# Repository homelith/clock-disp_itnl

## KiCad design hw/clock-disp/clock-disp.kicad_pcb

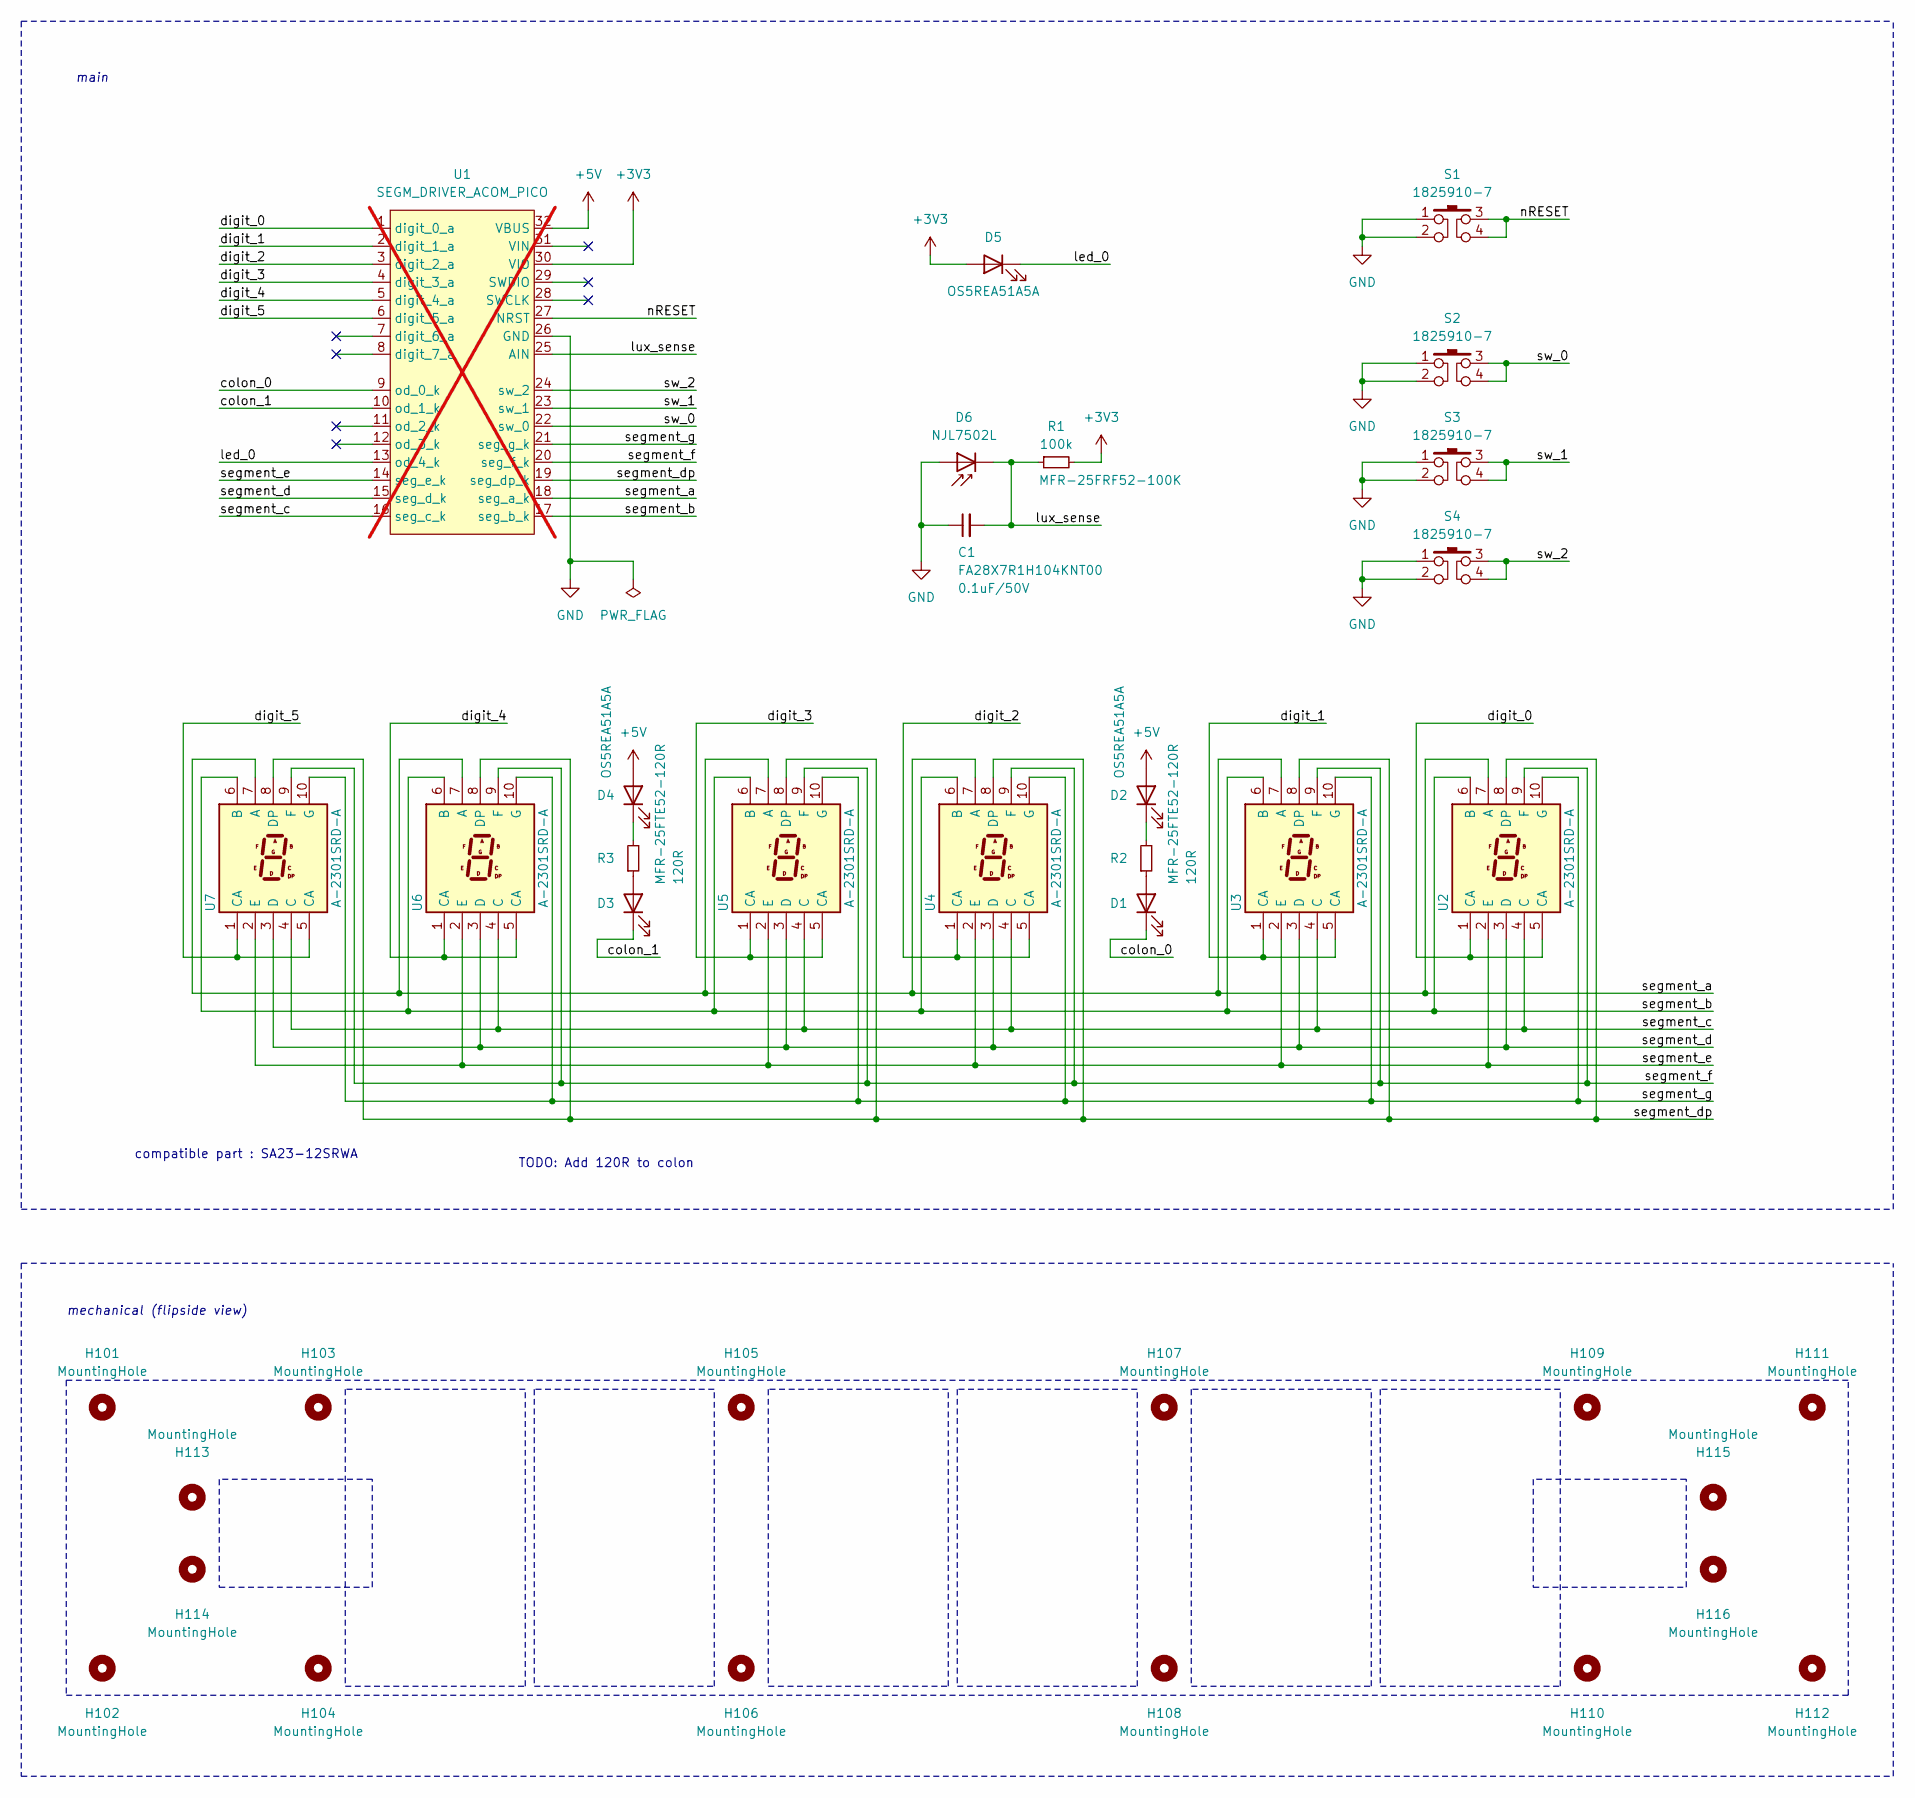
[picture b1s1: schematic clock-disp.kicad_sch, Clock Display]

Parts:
C1: FA28X7R1H104KNT00
D1, D2, D3, D4, D5: OS5REA51A5A
D6: NJL7502L
H101, H102, H103, H104, H105, H106, H107, H108, H109, H110, H111, H112, H113, H114, H115, H116: MountingHole; MountingHole_3.2mm_M3
R1: MFR-25FRF52-100K
R2, R3: MFR-25FTE52-120R
S1, S2, S3, S4: 1825910-7
U1: SEGM_DRIVER_ACOM_PICO; SEGM_DRIVER_ACOM_Pico; not fitted
U2, U3, U4, U5, U6, U7: A-2301SRD-A

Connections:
+3V3: D5.2 (A), R1.2, U1.30 (VIO)
+5V: D2.2 (A), D4.2 (A), U1.32 (VBUS)
/colon_0: D1.1 (K), U1.9 (od_0_k)
/colon_1: D3.1 (K), U1.10 (od_1_k)
/digit_0: U1.1 (digit_0_a), U2.1 (CA), U2.5 (CA)
/digit_1: U1.2 (digit_1_a), U3.1 (CA), U3.5 (CA)
/digit_2: U1.3 (digit_2_a), U4.1 (CA), U4.5 (CA)
/digit_3: U1.4 (digit_3_a), U5.1 (CA), U5.5 (CA)
/digit_4: U1.5 (digit_4_a), U6.1 (CA), U6.5 (CA)
/digit_5: U1.6 (digit_5_a), U7.1 (CA), U7.5 (CA)
/led_0: D5.1 (K), U1.13 (od_4_k)
/lux_sense: C1.2, D6.1 (K), R1.1, U1.25 (AIN)
/nRESET: S1.3, S1.4, U1.27 (NRST)
/segment_a: U1.18 (seg_a_k), U2.7 (A), U3.7 (A), U4.7 (A), U5.7 (A), U6.7 (A), U7.7 (A)
/segment_b: U1.17 (seg_b_k), U2.6 (B), U3.6 (B), U4.6 (B), U5.6 (B), U6.6 (B), U7.6 (B)
/segment_c: U1.16 (seg_c_k), U2.4 (C), U3.4 (C), U4.4 (C), U5.4 (C), U6.4 (C), U7.4 (C)
/segment_d: U1.15 (seg_d_k), U2.3 (D), U3.3 (D), U4.3 (D), U5.3 (D), U6.3 (D), U7.3 (D)
/segment_dp: U1.19 (seg_dp_k), U2.8 (DP), U3.8 (DP), U4.8 (DP), U5.8 (DP), U6.8 (DP), U7.8 (DP)
/segment_e: U1.14 (seg_e_k), U2.2 (E), U3.2 (E), U4.2 (E), U5.2 (E), U6.2 (E), U7.2 (E)
/segment_f: U1.20 (seg_f_k), U2.9 (F), U3.9 (F), U4.9 (F), U5.9 (F), U6.9 (F), U7.9 (F)
/segment_g: U1.21 (seg_g_k), U2.10 (G), U3.10 (G), U4.10 (G), U5.10 (G), U6.10 (G), U7.10 (G)
/sw_0: S2.3, S2.4, U1.22 (sw_0)
/sw_1: S3.3, S3.4, U1.23 (sw_1)
/sw_2: S4.3, S4.4, U1.24 (sw_2)
GND: C1.1, D6.2 (A), S1.1, S1.2, S2.1, S2.2, S3.1, S3.2, S4.1, S4.2, U1.26 (GND)
unnamed: D1.2 (A), R2.1
unnamed: D2.1 (K), R2.2
unnamed: D3.2 (A), R3.1
unnamed: D4.1 (K), R3.2

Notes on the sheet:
TODO: Add 120R to colon
compatible part : SA23-12SRWA
mechanical (flipside view)
main

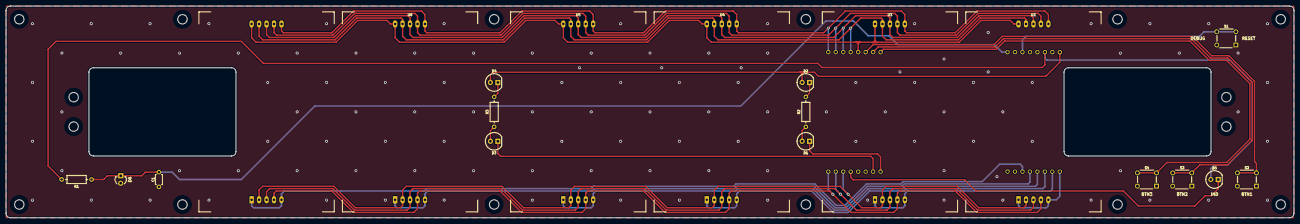
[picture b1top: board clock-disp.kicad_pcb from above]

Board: 2 copper layers, 438.0 x 72.0 mm, 37 parts (1 on the bottom side), 29 nets.

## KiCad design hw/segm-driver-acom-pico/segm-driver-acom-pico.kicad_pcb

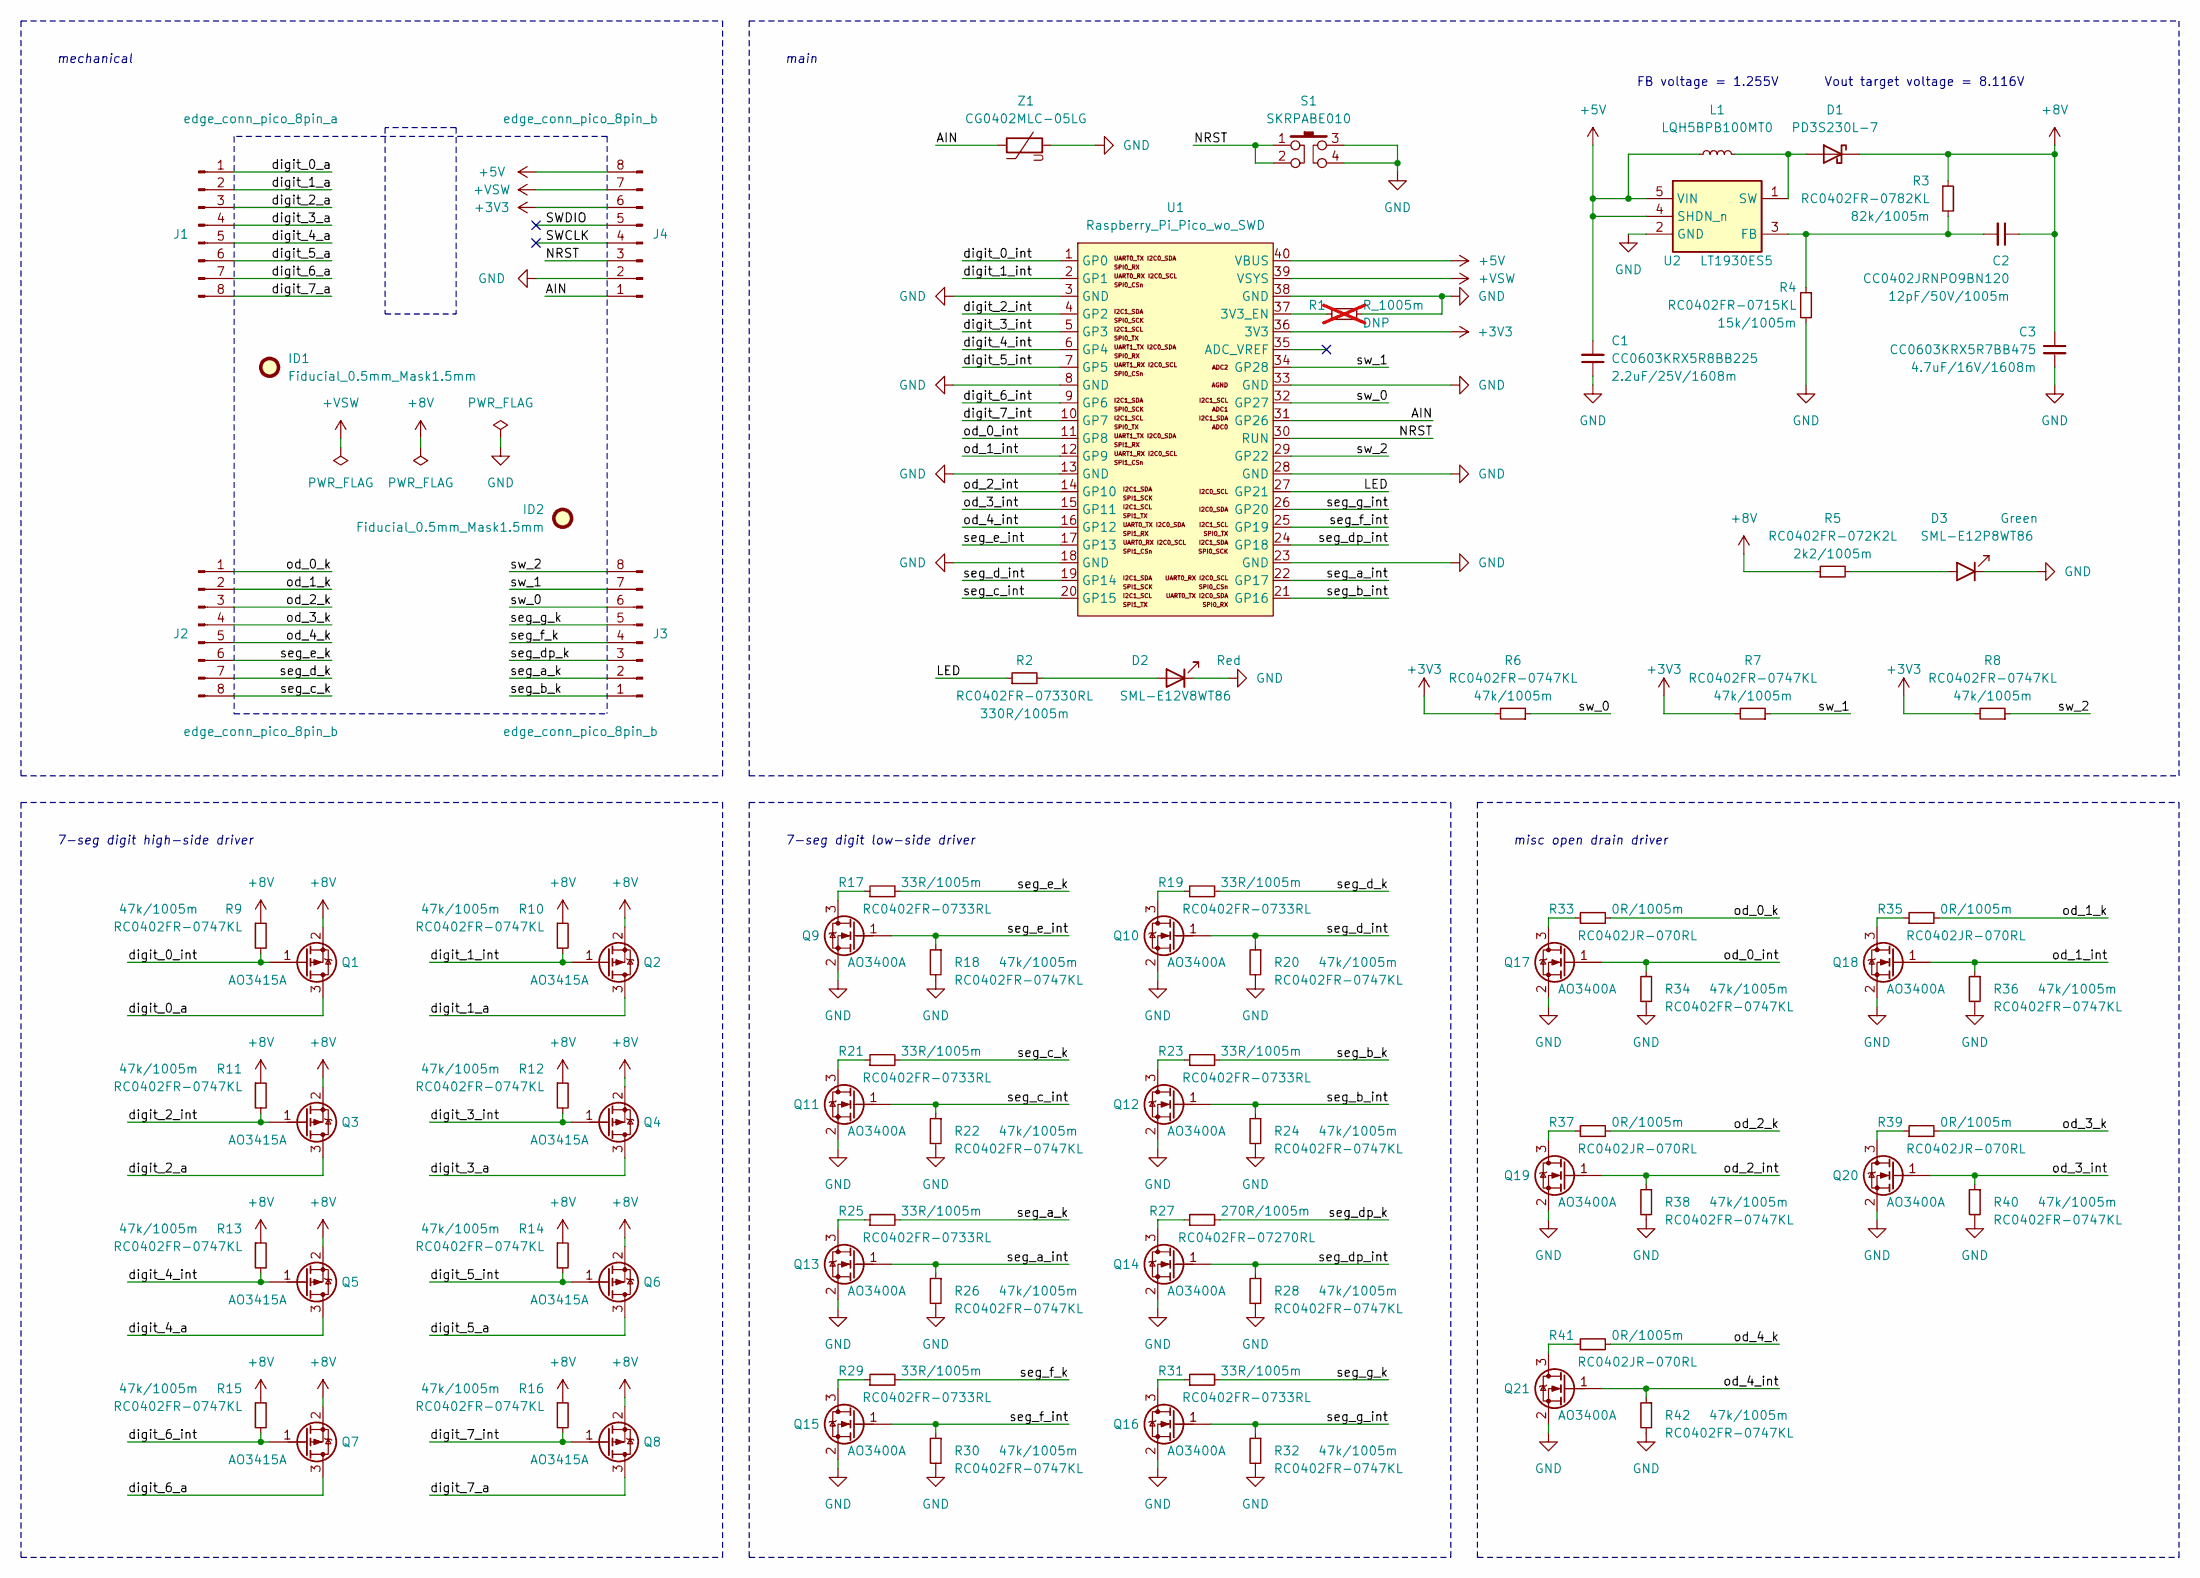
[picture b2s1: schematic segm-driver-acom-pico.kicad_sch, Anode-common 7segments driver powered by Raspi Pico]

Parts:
C1: CC0603KRX5R8BB225
C2: CC0402JRNPO9BN120
C3: CC0603KRX5R7BB475
D1: PD3S230L-7
D2: SML-E12V8WT86
D3: SML-E12P8WT86
ID1, ID2: Fiducial_0.5mm_Mask1.5mm
J1: edge_conn_pico_8pin_a
J2, J3, J4: edge_conn_pico_8pin_b
L1: LQH5BPB100MT0
Q1, Q2, Q3, Q4, Q5, Q6, Q7, Q8: AO3415A
Q9, Q10, Q11, Q12, Q13, Q14, Q15, Q16, Q17, Q18, Q19, Q20, Q21: AO3400A
R1: R_1005m; not fitted
R2: RC0402FR-07330RL
R3: RC0402FR-0782KL
R4: RC0402FR-0715KL
R5: RC0402FR-072K2L
R6, R7, R8, R9, R10, R11, R12, R13, R14, R15, R16, R18, R20, R22, R24, R26, R28, R30, R32, R34, R36, R38, R40, R42: RC0402FR-0747KL
R17, R19, R21, R23, R25, R29, R31: RC0402FR-0733RL
R27: RC0402FR-07270RL
R33, R35, R37, R39, R41: RC0402JR-070RL
S1: SKRPABE010
U1: Raspberry_Pi_Pico_wo_SWD
U2: LT1930ES5
Z1: CG0402MLC-05LG

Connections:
+3V3: J4.6, R6.2, R7.2, R8.2, U1.36 (3V3)
+5V: C1.2, J4.8, L1.1, U1.40 (VBUS), U2.4 (SHDN_n), U2.5 (VIN)
+8V: C2.1, C3.1, D1.2 (K), Q1.2 (S), Q2.2 (S), Q3.2 (S), Q4.2 (S), Q5.2 (S), Q6.2 (S), Q7.2 (S), Q8.2 (S), R3.1, R5.1, R9.1, R10.1, R11.1, R12.1, R13.1, R14.1, R15.1, R16.1
+VSW: J4.7, U1.39 (VSYS)
/AIN: J4.1, U1.31 (GP26), Z1.1
/LED: R2.1, U1.27 (GP21)
/NRST: J4.3, S1.1, S1.2, U1.30 (RUN)
/SWCLK: J4.4
/SWCLK_1: J4.4
/SWCLK_2: J4.4
/SWDIO: J4.5
/SWDIO_1: J4.5
/SWDIO_2: J4.5
/digit_0_a: J1.1, Q1.3 (D)
/digit_0_int: Q1.1 (G), R9.2, U1.1 (GP0)
/digit_1_a: J1.2, Q2.3 (D)
/digit_1_int: Q2.1 (G), R10.2, U1.2 (GP1)
/digit_2_a: J1.3, Q3.3 (D)
/digit_2_int: Q3.1 (G), R11.2, U1.4 (GP2)
/digit_3_a: J1.4, Q4.3 (D)
/digit_3_int: Q4.1 (G), R12.2, U1.5 (GP3)
/digit_4_a: J1.5, Q5.3 (D)
/digit_4_int: Q5.1 (G), R13.2, U1.6 (GP4)
/digit_5_a: J1.6, Q6.3 (D)
/digit_5_int: Q6.1 (G), R14.2, U1.7 (GP5)
/digit_6_a: J1.7, Q7.3 (D)
/digit_6_int: Q7.1 (G), R15.2, U1.9 (GP6)
/digit_7_a: J1.8, Q8.3 (D)
/digit_7_int: Q8.1 (G), R16.2, U1.10 (GP7)
/od_0_int: Q17.1 (G), R34.1, U1.11 (GP8)
/od_0_k: J2.1, R33.2
/od_1_int: Q18.1 (G), R36.1, U1.12 (GP9)
/od_1_k: J2.2, R35.2
/od_2_int: Q19.1 (G), R38.1, U1.14 (GP10)
/od_2_k: J2.3, R37.2
/od_3_int: Q20.1 (G), R40.1, U1.15 (GP11)
/od_3_k: J2.4, R39.2
/od_4_int: Q21.1 (G), R42.1, U1.16 (GP12)
/od_4_k: J2.5, R41.2
/seg_a_int: Q13.1 (G), R26.1, U1.22 (GP17)
/seg_a_k: J3.2, R25.2
/seg_b_int: Q12.1 (G), R24.1, U1.21 (GP16)
/seg_b_k: J3.1, R23.2
/seg_c_int: Q11.1 (G), R22.1, U1.20 (GP15)
/seg_c_k: J2.8, R21.2
/seg_d_int: Q10.1 (G), R20.1, U1.19 (GP14)
/seg_d_k: J2.7, R19.2
/seg_dp_int: Q14.1 (G), R28.1, U1.24 (GP18)
/seg_dp_k: J3.3, R27.2
/seg_e_int: Q9.1 (G), R18.1, U1.17 (GP13)
/seg_e_k: J2.6, R17.2
/seg_f_int: Q15.1 (G), R30.1, U1.25 (GP19)
/seg_f_k: J3.4, R29.2
/seg_g_int: Q16.1 (G), R32.1, U1.26 (GP20)
/seg_g_k: J3.5, R31.2
/sw_0: J3.6, R6.1, U1.32 (GP27)
/sw_1: J3.7, R7.1, U1.34 (GP28)
/sw_2: J3.8, R8.1, U1.29 (GP22)
GND: C1.1, C3.2, D2.1 (K), D3.1 (K), J4.2, Q9.2 (S), Q10.2 (S), Q11.2 (S), Q12.2 (S), Q13.2 (S), Q14.2 (S), Q15.2 (S), Q16.2 (S), Q17.2 (S), Q18.2 (S), Q19.2 (S), Q20.2 (S), Q21.2 (S), R1.2, R4.2, R18.2, R20.2, R22.2, R24.2, R26.2, R28.2, R30.2, R32.2, R34.2, R36.2, R38.2, R40.2, R42.2, S1.3, S1.4, U1.3 (GND), U1.8 (GND), U1.13 (GND), U1.18 (GND), U1.23 (GND), U1.28 (GND), U1.33 (GND), U1.38 (GND), U2.2 (GND), Z1.2
unnamed: D1.1 (A), L1.2, U2.1 (SW)
unnamed: D2.2 (A), R2.2
unnamed: D3.2 (A), R5.2
unnamed: Q9.3 (D), R17.1
unnamed: Q10.3 (D), R19.1
unnamed: Q11.3 (D), R21.1
unnamed: Q12.3 (D), R23.1
unnamed: Q13.3 (D), R25.1
unnamed: Q14.3 (D), R27.1
unnamed: Q15.3 (D), R29.1
unnamed: Q16.3 (D), R31.1
unnamed: Q17.3 (D), R33.1
unnamed: Q18.3 (D), R35.1
unnamed: Q19.3 (D), R37.1
unnamed: Q20.3 (D), R39.1
unnamed: Q21.3 (D), R41.1
unnamed: R1.1, U1.37 (3V3_EN)
unnamed: C2.2, R3.2, R4.1, U2.3 (FB)

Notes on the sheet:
7-seg digit high-side driver
7-seg digit low-side driver
mechanical
FB voltage = 1.255V
Vout target voltage = 8.116V
misc open drain driver
main

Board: 2 copper layers, 80 parts (0 on the bottom side), 71 nets, no tracks yet.
